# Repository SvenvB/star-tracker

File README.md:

# DIY Sidereal Star Tracker for the EQ-13 mount (Orion SpaceProbe 130ST telescope)

I'm using the [Orion SpaceProbe 130ST telescope](https://www.highpointscientific.com/orion-spaceprobe-130st-short-tube-eq-reflector-telescope) with a [ZWO ASI224MC](https://www.zwoastro.com/product/zwo-asi224mc/) CMOS imaging camera and enjoy deep-sky imaging without breaking the bank. I got the telescope right before Orion ceased to exist and was therefore unable to purchase their [electronic tracking drive](https://www.amazon.com/Orion-Electronic-Tracking-Drive-Mount/dp/B0B9GHRXKY/ref=zg_bs_g_3426091_d_sccl_18/139-5786178-3062238?psc=1) for the [EQ-13 mount](https://optcorp.com/products/orion-eq-13-equatorial-telescope-mount-and-tripod?srsltid=AfmBOooOyh1JBukKWYQKR0jKjXO8pRvacwGi2XBEpK7pBYKymDbFRSgW) that came with the telescope. As a result, I decided to make a simple driver myself. The total price was around $50 (I am not fully sure since I had various components already in house), with the cost dominated by the stepper motor (~$30).

The star tracker is powered by a 12 V source using 8× 1.5 V AA batteries. This power source is also used for my [Flat Frame Light Diffuser](https://github.com/SvenvB/Flat-frame-light-diffuser). The battery pack lasts at least one or two full nights imaging.

With this motor, I’ve been able to consistently achieve good tracking for exposure times of up to 5 seconds without noticeable star trailing. For example, see the stacked result of a 140-frame, 5-second exposure of the M27 Dumbbell Nebula:

The exposure time can be pushed up to 20 seconds, as I tried recently when imaging the M51 Whirlpool Galaxy and M104 Sombrero Galaxy. At this exposure time, I had to discard about 50% of the frames due to noticeable star trailing, but the results were still quite nice:

**M51 Whirlpool Galaxy using 49 frames at 20-second exposure:**

**M104 Sombrero Galaxy using 162 frames at 20-second exposure:**

Keep in mind that the EQ-13 mount is very flimsy, so the effective tracking speed can be inconsistent and occasionally needs to be fine-tuned with the rotary encoder. Properly balancing the telescope with the counterweight is also important.

The star tracker has two modes: **Tracking** (sidereal speed) and **Slewing** (for quick repointing). Both speeds can be fine-tuned with the rotary encoder. Clicking the encoder resets the speed to its default value.

---

## Materials

* **Stepper motor** – The [17HS19-1684S-PG51](https://www.omc-stepperonline.com/nema-17-stepper-motor-bipolar-l-48mm-w-gear-ratio-51-1-planetary-gearbox-17hs19-1684s-pg51) has an 51:1 gear ratio Planetary Gearbox and 0.035 deg / step. 
* **[A4988 stepper motor driver](https://www.aliexpress.us/item/3256805793855652.html?src=google&pdp_npi=4%40dis%21USD%215.81%211.80%21%21%21%21%21%40%2112000035152956725%21ppc%21%21%21&src=google&albch=shopping&acnt=708-803-3821&isdl=y&slnk=&plac=&mtctp=&albbt=Google_7_shopping&aff_platform=google&aff_short_key=UneMJZVf&gclsrc=aw.ds&albagn=888888&ds_e_adid=&ds_e_matchtype=&ds_e_device=c&ds_e_network=x&ds_e_product_group_id=&ds_e_product_id=en3256805793855652&ds_e_product_merchant_id=5080850986&ds_e_product_country=US&ds_e_product_language=en&ds_e_product_channel=online&ds_e_product_store_id=&ds_url_v=2&albcp=19623912707&albag=&isSmbAutoCall=false&needSmbHouyi=false&gad_source=4&gad_campaignid=19616013570&gbraid=0AAAAAD6I-hHBkOKXJMnzFfLlYu7H2lh_F&gclid=CjwKCAjw3f_BBhAPEiwAaA3K5M1DYmCJJrGB-SmIvHADkCwvgrs8LZ0YxJ87CBh64NpMWFss14TvOhoCS8UQAvD_BwE&gatewayAdapt=glo2usa)** - with heatsink  
* **[Arduino Nano](https://www.aliexpress.us/item/3256805941736729.html?src=google&pdp_npi=4%40dis%21USD%211.40%211.40%21%21%21%21%21%40%2112000035881712633%21ppc%21%21%21&src=google&albch=shopping&acnt=708-803-3821&isdl=y&slnk=&plac=&mtctp=&albbt=Google_7_shopping&aff_platform=google&aff_short_key=UneMJZVf&gclsrc=aw.ds&albagn=888888&ds_e_adid=&ds_e_matchtype=&ds_e_device=c&ds_e_network=x&ds_e_product_group_id=&ds_e_product_id=en3256805941736729&ds_e_product_merchant_id=5293204312&ds_e_product_country=US&ds_e_product_language=en&ds_e_product_channel=online&ds_e_product_store_id=&ds_url_v=2&albcp=20546179873&albag=&isSmbAutoCall=false&needSmbHouyi=false&gad_source=1&gad_campaignid=17337505674&gbraid=0AAAAAD6I-hH9Do3V7PLbSMgWzNnF9Df5B&gclid=CjwKCAjw3f_BBhAPEiwAaA3K5HHcGXW2QnrE5iamtjPykZQPZXEYG24YuaDJb-yKoQAY5awy_wlY_hoCS_MQAvD_BwE&gatewayAdapt=glo2usa)**  
* **KY-040 Rotary Encoder** - with clickable switch
* **[AMS1117-5.0V voltage regulator](https://www.aliexpress.us/item/3256803404676437.html?src=google&pdp_npi=4%40dis%21USD%210.81%210.71%21%21%21%21%21%40%2112000036726215299%21ppc%21%21%21&src=google&albch=shopping&acnt=708-803-3821&isdl=y&slnk=&plac=&mtctp=&albbt=Google_7_shopping&aff_platform=google&aff_short_key=UneMJZVf&gclsrc=aw.ds&albagn=888888&ds_e_adid=&ds_e_matchtype=&ds_e_device=c&ds_e_network=x&ds_e_product_group_id=&ds_e_product_id=en3256803404676437&ds_e_product_merchant_id=108821505&ds_e_product_country=US&ds_e_product_language=en&ds_e_product_channel=online&ds_e_product_store_id=&ds_url_v=2&albcp=19108228023&albag=&isSmbAutoCall=false&needSmbHouyi=false&gad_source=1&gad_campaignid=19108292148&gbraid=0AAAAAD6I-hEQvsbF3m6vS52BjuQyr5Sz-&gclid=CjwKCAjw3f_BBhAPEiwAaA3K5JJGzJ1sDHvnzFAuJfsHekJ_CBdko_NY7DRJxSJSMnykyhvmJW4OUBoCTr8QAvD_BwE&gatewayAdapt=glo2usa)**
* **100 uF radial electrolytic capacitor** - for A4988 protection
* **4x through hole 5mm LEDs** - Three to indicate the motor mode and one to indicate that the controller is powered.
* **6x SMD 0805 resistors** - 4x for LED loading (~1 kOhm) and 2x pull-up resistors for the switch (>5 kOhm).
* **2A glass tube fuse and [fuse holder](https://www.amazon.com/dp/B074N1NMMX?ref_=ppx_hzsearch_conn_dt_b_fed_asin_title_1)** - for A4988 protection. The holder has 15mm pin spacing and can hold a 5x20mm fuse.
* **[5.5x2.1mm DC barrel jack](https://www.amazon.com/dp/B081DYQSC9/ref=pe_386300_440135490_TE_simp_item_image?th=1)** - for controller power supply
* **[4 pin aviation plug](https://www.amazon.com/dp/B07ZP725YD/ref=pe_386300_440135490_TE_simp_item_image)** - for connecting the stepper motor
* **[3 position rocker switch](https://www.aliexpress.us/item/2251832521009333.html?spm=a2g0o.order_list.order_list_main.80.21ef1802ewc4Qe&gatewayAdapt=glo2usa)** - for motor mode selection
* **2 position rocker switch** - for controller power ON/OFF
* **2x 5-pin JST connectors** - male and female for connecting the rotary encoder and Switch-and-LED board
* **2x 2-pin JST connectors** - male and female for connecting the power rocker switch and power to the Switch-and-LED board.
* **4-pin JST connector**  - male and female for connecting the aviation plug.
* **[8x AA battery holder](https://www.amazon.com/dp/B09LTSNJTW/ref=pe_386300_440135490_TE_simp_item_image)** - with 5.5x2.1mm Male Jack Connector
* **various screws** - to mount the PCBs to the casing and top-plate, to mount the top-plate to the casing, to connect the stepper motor to the 3D-printed mount, to prevent the 3D-printed coupling piece from slipping on the worm gear shaft, to connect the 3D-printed mount to the EQ-13 body.
* **3D printer and filament** - for the motor mount and controller box.

**Optional**
* **Capacitors** - at the output of the voltage regulator to reduce power supply noise. I used a 10 uF radial and 100 nF + 10 nF ceramic disc capacitors in parallel. 
* **Cable sleeve** - to organize the stepper motor wires.
* **3-pin screw terminal** - mounted on the switch-and-LED board, to easily connect and disconnect the 3-position rocker switch.

---

## Instructions

### 1. Calculate Stepper Motor Requirements

- Stepper motors are highly accurate and provide high torque, making them ideal for this application. A typical stepper motor has 200 steps per revolution (1.8°/step).
- I tested that the Right Ascension (RA) knob on the EQ-13 mount must be rotated about 5.5 times to move 1 hour in RA. This corresponds to roughly 132 revolutions over 24 h in RA, i.e., a worm gear ratio of 132:1.
- One sidereal day is 23h 56m 4s, or 86,164 seconds. Therefore, the worm gear should rotate at ~0.55°/s. Since a typical stepper motor would move only once every 3+ seconds at this rate, a gearbox is needed.
- Choosing a low gear ratio results in jerky tracking, while too high a gear ratio limits slewing speed.
- I chose the [17HS19-1684S-PG51](https://www.omc-stepperonline.com/nema-17-stepper-motor-bipolar-l-48mm-w-gear-ratio-51-1-planetary-gearbox-17hs19-1684s-pg51) stepper motor with a 51:1 gearbox. This gives a tracking speed of ~15.6 steps per second, which I would not recommend going below.

**RA worm gear visible in the picture below:**

---

### 2. Electrical Design

The controller uses two PCBs:

1. **Switch-and-LED board** – Mounted to the front plate. This board connects to the 3-position rocker switch, integrates pull-up resistors, and drives LEDs indicating the motor mode. It is reused from another project that daisy-chains the power pins two multiple boards.
2. **Controller board** – Mounted to the bottom of the casing. This board contains the Arduino, stepper motor driver, and supporting components.

Boards were designed in KiCAD. Gerber files are attached, and PCBs were ordered via JLCPCB.

#### Switch-and-LED Board
* The pin-headers shown below are not needed. You can directly solder the cables to the PCB, as is shown in the *Assembled Control Box* photograph in Section 4 below. 
* The schematic indicates LED resistors of 470 Ohm. However, I have found that the LEDs are too bright with those values. I recommend increasing them. 

*KiCAD Schematic:*

*KiCAD 3D View:*

#### Controller Board

- Be sure to include the 100 µF capacitor. The A4988 can produce voltage spikes due to back-EMF from the stepper motor’s inductance. This capacitor helps absorb those spikes, protecting the driver. Place the capacitor as close to the driver as is possible.
- The capacitors at the AMS1117 output are optional.
- Use the method described [here](https://www.pololu.com/product/1182) to limit the A4988 current to your motor’s rated current (1.68 A/phase for mine).
- I have not employed microstepping to increase the number of steps per second. The motor might operate more smoothly if we half the step. However, it will mean tighter timing and more processing overhead for the Arduino, and a reduced torque per microstep. If the mount is imbalanced the torque might not be adequate. Something to be tested.

*KiCAD Schematic:*

*KiCAD 3D View:*

*Assembled Controller Photo:*

---

### 3. CAD Design

- The control box and motor mount were designed in FreeCAD. Design files and .STLs are attached.
- The coupling piece between the stepper motor and worm gear shaft (green part in the image) must fit very tightly to avoid backlash.
- You will need a screw to mate the coupling piece to the worm gear shaft. 

*FreeCAD View – Control Box (Closed):*

*FreeCAD View – Control Box (Open):*

*FreeCAD View – Motor Mount:*

---

### 4. Assembly

- Mount the PCBs to the casing and top plate using screws.
- Avoid contact between wires and the heatsink of the stepper motor driver.

*Assembled Control Box:*

*Assembled Stepper Motor:*

---

### 5. Arduino Coding and Operation

- The Arduino is programmed using the standard Arduino IDE. Code is available [here](./Arduino/RA_Controller_V3/RA_Controller_V3.ino).
- I found the most stable tracking at 16.3 steps/second, close to the calculated 15.6 steps/sec sidereal speed.
- In **Tracking mode**, each rotary tick changes the speed by ±0.1 steps/sec.
- In **Slewing mode**, each tick changes the speed by ±1× sidereal rate. Slewing is possible in both RA directions.
- Clicking the rotary encoder resets the speed to its default value.

**Clear skies!**

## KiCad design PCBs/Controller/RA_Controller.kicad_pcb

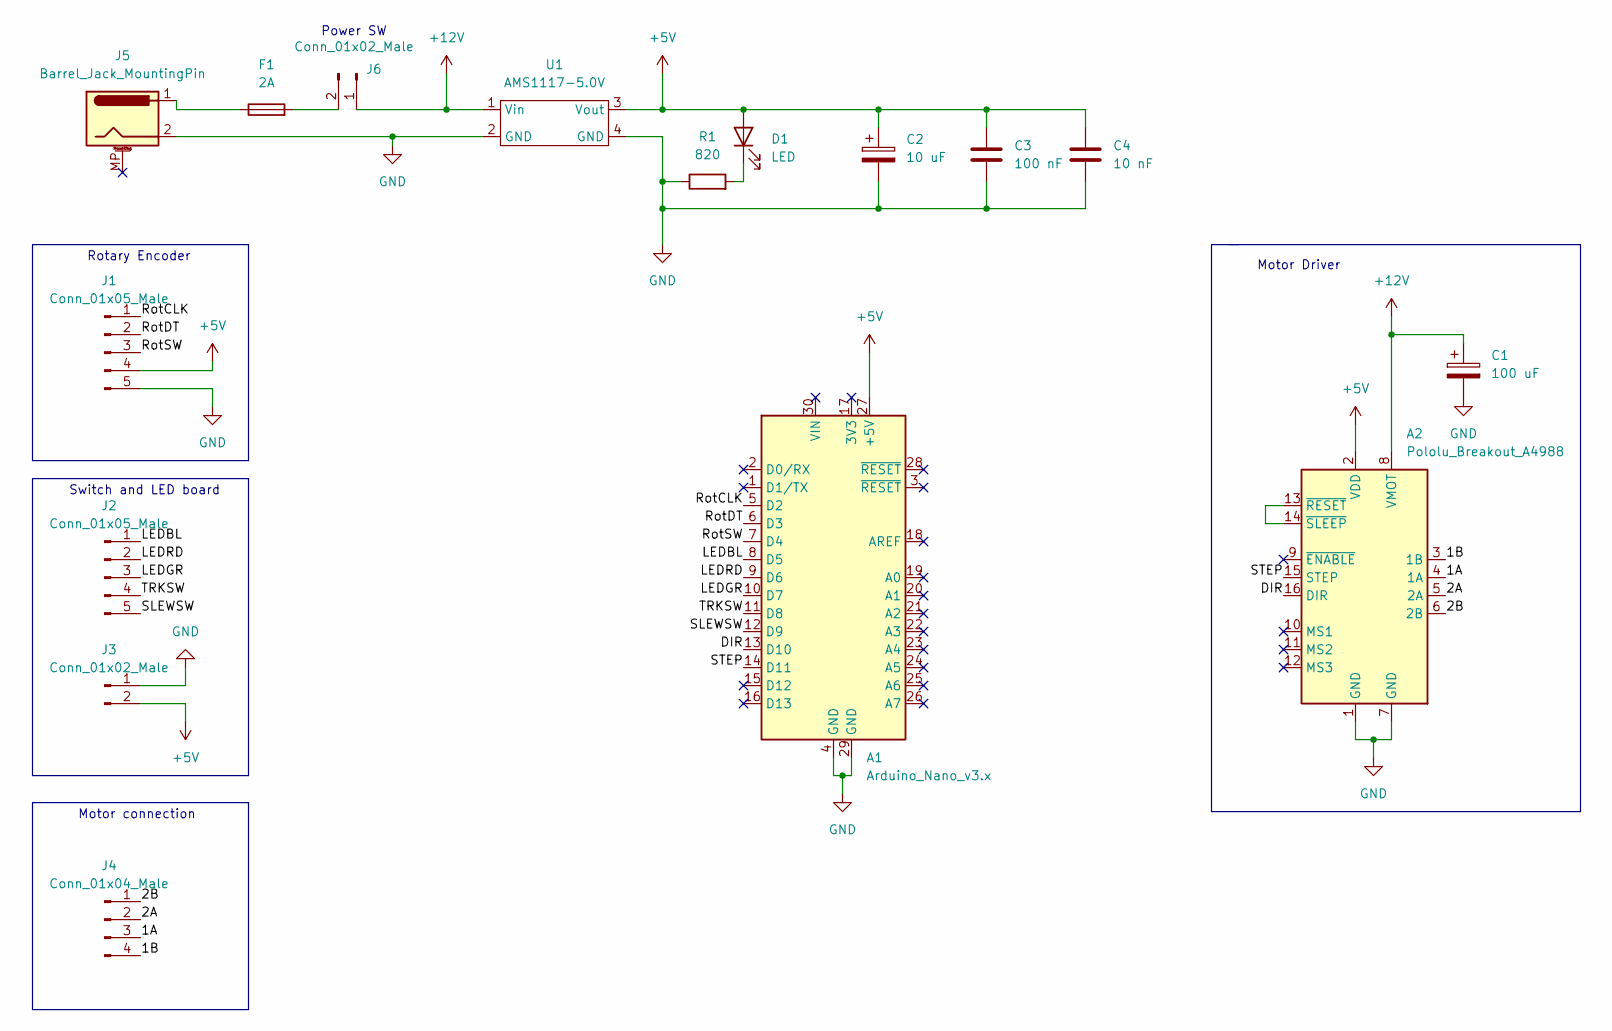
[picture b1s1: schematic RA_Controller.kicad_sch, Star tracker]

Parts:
A1: Arduino_Nano_v3.x; Arduino_Nano
A2: Pololu_Breakout_A4988; Pololu_Breakout-16_15.2x20.3mm
C1: 100 uF; CP_Radial_D6.3mm_P2.50mm
C2: 10 uF; CP_Radial_D6.3mm_P2.50mm
C3: 100 nF; C_Disc_D5.1mm_W3.2mm_P5.00mm
C4: 10 nF; C_Disc_D3.8mm_W2.6mm_P2.50mm
D1: LED; LED_D5.0mm
F1: 2A; LED_D5.0mm
J1, J2: Conn_01x05_Male; JST_XH_B5B-XH-A_1x05_P2.50mm_Vertical
J3, J6: Conn_01x02_Male; JST_XH_B2B-XH-A_1x02_P2.50mm_Vertical
J4: Conn_01x04_Male; JST_XH_B4B-XH-A_1x04_P2.50mm_Vertical
J5: Barrel_Jack_MountingPin; BarrelJack_Horizontal
R1: 820; R_0805_2012Metric_Pad1.20x1.40mm_HandSolder
U1: AMS1117-5.0V

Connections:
+5V: A1.27 (+5V), A2.2 (VDD), C2.1, C3.1, C4.1, D1.2 (A), J1.4, J3.2, U1.3 (Vout)
+12V: A2.8 (VMOT), C1.1, J6.1, U1.1 (Vin)
/1A: A2.4 (1A), J4.3
/1B: A2.3 (1B), J4.4
/2A: A2.5 (2A), J4.2
/2B: A2.6 (2B), J4.1
/DIR: A1.13 (D10), A2.16 (DIR)
/LEDBL: A1.8 (D5), J2.1
/LEDGR: A1.10 (D7), J2.3
/LEDRD: A1.9 (D6), J2.2
/RotCLK: A1.5 (D2), J1.1
/RotDT: A1.6 (D3), J1.2
/RotSW: A1.7 (D4), J1.3
/SLEWSW: A1.12 (D9), J2.5
/STEP: A1.14 (D11), A2.15 (STEP)
/TRKSW: A1.11 (D8), J2.4
GND: A1.4 (GND), A1.29 (GND), A2.1 (GND), A2.7 (GND), C1.2, C2.2, C3.2, C4.2, J1.5, J3.1, J5.2, R1.1, U1.2 (GND), U1.4 (GND)
unnamed: A2.13 (~RESET), A2.14 (~SLEEP)
unnamed: D1.1 (K), R1.2
unnamed: F1.1, J5.1
unnamed: F1.2, J6.2

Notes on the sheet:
Motor connection
Motor Driver
Switch and LED board
Power SW
Rotary Encoder

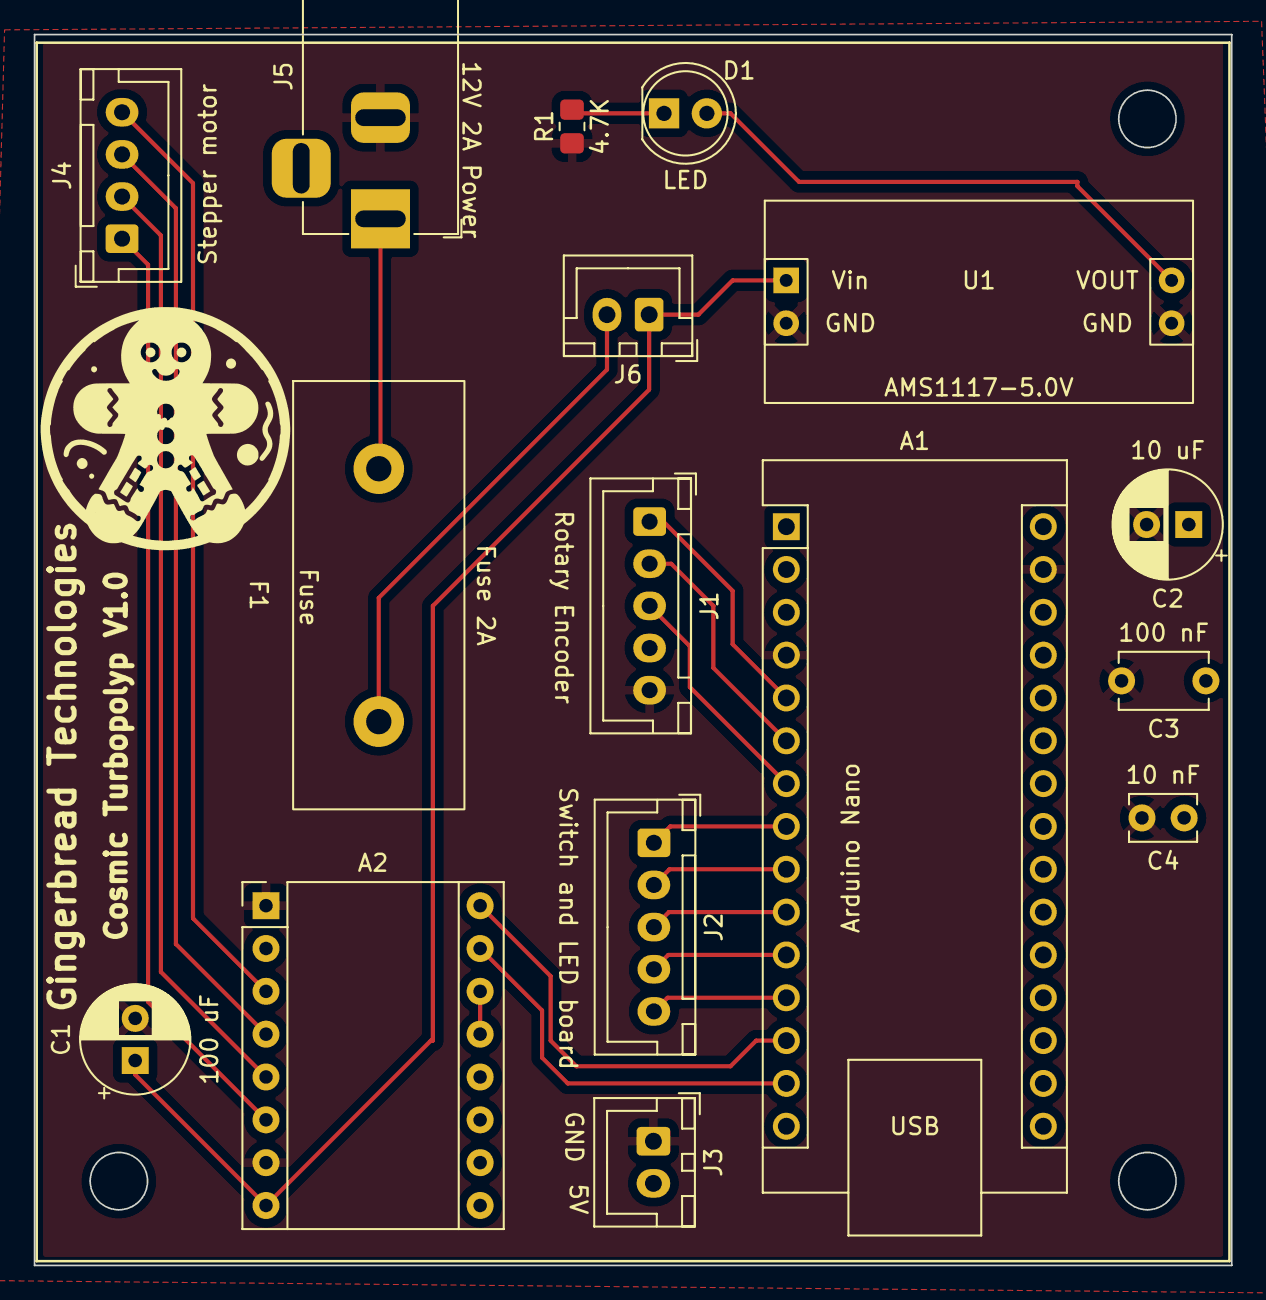
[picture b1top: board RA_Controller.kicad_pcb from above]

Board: 2 copper layers, 71.0 x 73.0 mm, 16 parts (0 on the bottom side), 21 nets.

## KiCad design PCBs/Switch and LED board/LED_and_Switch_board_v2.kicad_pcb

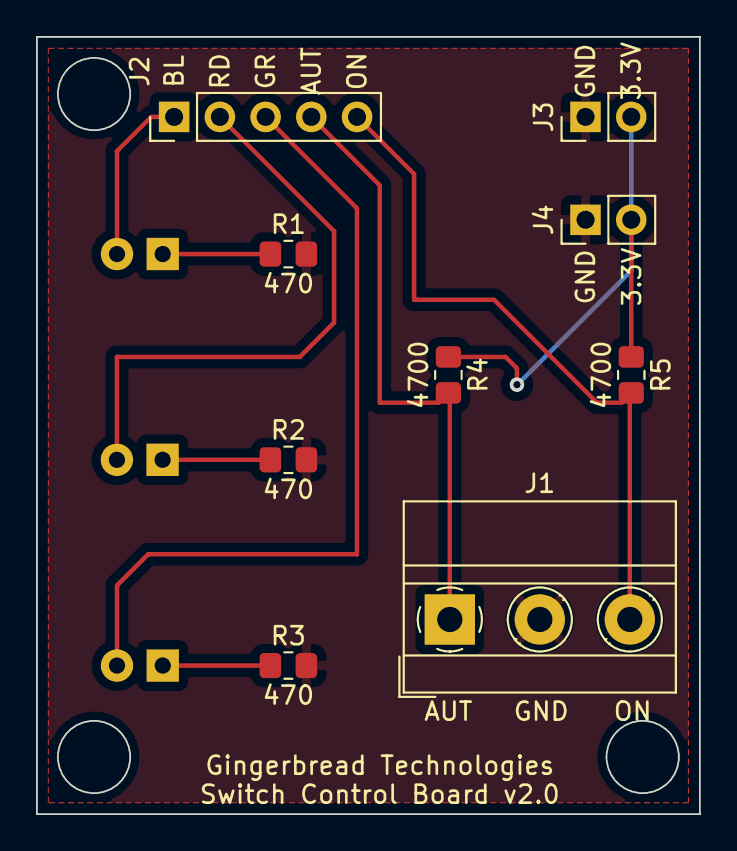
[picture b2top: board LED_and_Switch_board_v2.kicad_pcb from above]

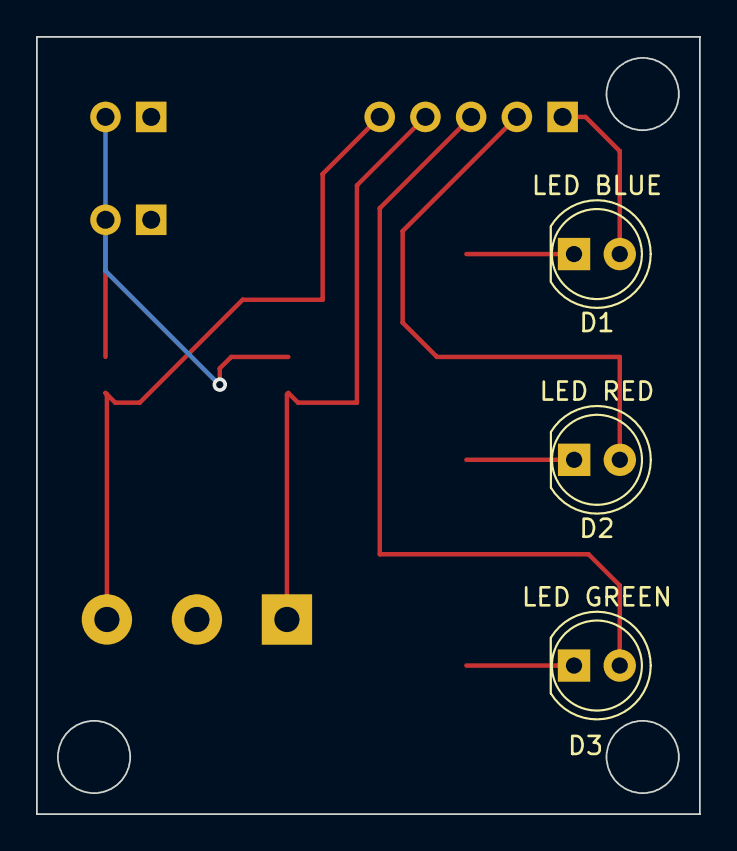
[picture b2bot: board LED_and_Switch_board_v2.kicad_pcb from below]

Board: 2 copper layers, 36.8 x 43.2 mm, 12 parts (3 on the bottom side), 10 nets.

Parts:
D1: LED BLUE; LED_D5.0mm
D2: LED RED; LED_D5.0mm
D3: LED GREEN; LED_D5.0mm
J1: Screw_Terminal_01x03; TerminalBlock_MetzConnect_Type011_RT05503HBWC_1x03_P5.00mm_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
J2: Conn_01x05_Female; PinHeader_1x05_P2.54mm_Vertical
J3, J4: Conn_01x02_Female; PinHeader_1x02_P2.54mm_Vertical
R1, R2, R3: 470; R_0805_2012Metric_Pad1.20x1.40mm_HandSolder
R4, R5: 4700; R_0805_2012Metric_Pad1.20x1.40mm_HandSolder

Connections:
+3.3V: J3.2, J4.2, R4.1, R5.1
GND: J1.2, J3.1, J4.1, R1.2, R2.2, R3.2
unnamed: D1.1 (K), R1.1
unnamed: D1.2 (A), J2.1
unnamed: D2.1 (K), R2.1
unnamed: D2.2 (A), J2.2
unnamed: D3.1 (K), R3.1
unnamed: D3.2 (A), J2.3
unnamed: J1.1, J2.4, R4.2
unnamed: J1.3, J2.5, R5.2

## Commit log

2025-06-05 Updated readme and content
2025-06-05 Update README.md
    Added details of the EQ-13 mount.
